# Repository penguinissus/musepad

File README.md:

# Musepad
This is a macropad that is built for helping with complicated functions when writing music in MuseScore. This macropad also features a compact and minimalistic design so it looks nice, and a plateless design which uses less material and provides more flex to each individual key.  

# User Instructions
Assembly:  
1. print out and buy all the parts found in `MusePad BOM.csv`   
2. solder everything together  
3. put in the keycaps accordingly (please refer to `3d models prints/Full Assembly.step` or reference pictures below for ideal layout)  
4. connect the oled to the pins on the PCB using jumper wires
5. sandwich pcb between the top and the bottom case  

Firmware:  
1. go to [circuitpython.org/downloads](circuitpython.org/downloads)    
2. download circuitpython for raspberry pi pico  
3. plug in keyboard to laptop and make sure to use a data transmitting cable  
4. open up the pico folder in your computer's directory  
5. replace the content of `code.py` in the pico folder with the one in this repo (`root://code/code.py`) 

# Why and how did I make it
I love composing music, and MuseScore is one great free composing software. However, whenever I want to compose efficiently, musescore hinders me significantly. Each detail I add to the music either requires too much shortcut memorization or it would take ages to find so I built MusePad to solve this problem. 

I first came up with some drawings of the design to make sure I knew how the layout kind of looked like. Then I made the schematic and PCB design on keycad, mostly following a tutorial (refer to the first resource link). I made the CAD on onshape mostly using skills I already had based on my past experiences, and for details that I don't really know, I referenced the hackpad guide (link no.2 in resource section). I also learned how to cad a keycap following a youtube tutorial (link no.3) which was really interesting. 

# Diagrams
Schematic Diagram:  
  
PCB Editor View:  
  
PCB Model:  
  
Assembled Model:  

# Resources
1. the   
2.   
3.

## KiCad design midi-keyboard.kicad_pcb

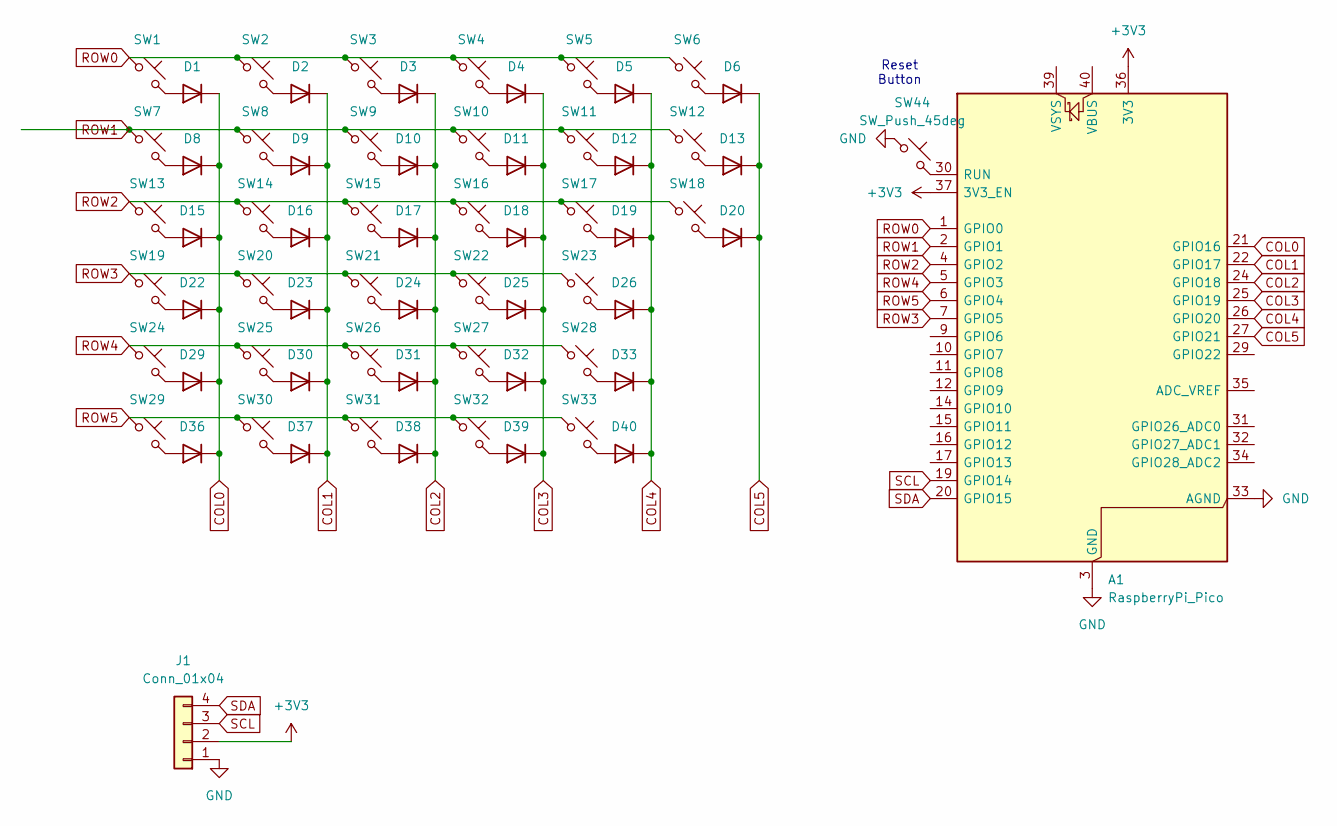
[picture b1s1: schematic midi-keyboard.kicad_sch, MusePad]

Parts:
A1: RaspberryPi_Pico; RaspberryPi_Pico_Common_THT
D1, D2, D3, D4, D5, D6, D8, D9, D10, D11, D12, D13, D15, D16, D17, D18, D19, D20, D22, D23, D24, D25, D26, D29, D30, D31, D32, D33, D36, D37, D38, D39, D40: 1N4148; D_DO-35_SOD27_P7.62mm_Horizontal
J1: Conn_01x04; PinSocket_1x04_P2.54mm_Vertical
SW1, SW2, SW3, SW4, SW5, SW6, SW7, SW8, SW9, SW10, SW11, SW12, SW13, SW14, SW15, SW16, SW17, SW18, SW19, SW20, SW21, SW22, SW23, SW24, SW25, SW26, SW27, SW28, SW29, SW30, SW31, SW32, SW33: SW_Push_45deg; SW_Cherry_MX_1.00u_PCB
SW44: SW_Push_45deg; SW_PUSH_6mm

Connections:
+3V3: A1.36 (3V3), A1.37 (3V3_EN), J1.2
COL0: A1.21 (GPIO16), D1.1 (K), D8.1 (K), D15.1 (K), D22.1 (K), D29.1 (K), D36.1 (K)
COL1: A1.22 (GPIO17), D2.1 (K), D9.1 (K), D16.1 (K), D23.1 (K), D30.1 (K), D37.1 (K)
COL2: A1.24 (GPIO18), D3.1 (K), D10.1 (K), D17.1 (K), D24.1 (K), D31.1 (K), D38.1 (K)
COL3: A1.25 (GPIO19), D4.1 (K), D11.1 (K), D18.1 (K), D25.1 (K), D32.1 (K), D39.1 (K)
COL4: A1.26 (GPIO20), D5.1 (K), D12.1 (K), D19.1 (K), D26.1 (K), D33.1 (K), D40.1 (K)
COL5: A1.27 (GPIO21), D6.1 (K), D13.1 (K), D20.1 (K)
GND: A1.3 (GND), A1.8 (GND), A1.13 (GND), A1.18 (GND), A1.23 (GND), A1.28 (GND), A1.33 (AGND), A1.38 (GND), J1.1, SW44.1
unnamed: A1.30 (RUN), SW44.2
unnamed: D1.2 (A), SW1.2
unnamed: D2.2 (A), SW2.2
unnamed: D3.2 (A), SW3.2
unnamed: D4.2 (A), SW4.2
unnamed: D5.2 (A), SW5.2
unnamed: D6.2 (A), SW6.2
unnamed: D8.2 (A), SW7.2
unnamed: D9.2 (A), SW8.2
unnamed: D10.2 (A), SW9.2
unnamed: D11.2 (A), SW10.2
unnamed: D12.2 (A), SW11.2
unnamed: D13.2 (A), SW12.2
unnamed: D15.2 (A), SW13.2
unnamed: D16.2 (A), SW14.2
unnamed: D17.2 (A), SW15.2
unnamed: D18.2 (A), SW16.2
unnamed: D19.2 (A), SW17.2
unnamed: D20.2 (A), SW18.2
unnamed: D22.2 (A), SW19.2
unnamed: D23.2 (A), SW20.2
unnamed: D24.2 (A), SW21.2
unnamed: D25.2 (A), SW22.2
unnamed: D26.2 (A), SW23.2
unnamed: D29.2 (A), SW24.2
unnamed: D30.2 (A), SW25.2
unnamed: D31.2 (A), SW26.2
unnamed: D32.2 (A), SW27.2
unnamed: D33.2 (A), SW28.2
unnamed: D36.2 (A), SW29.2
unnamed: D37.2 (A), SW30.2
unnamed: D38.2 (A), SW31.2
unnamed: D39.2 (A), SW32.2
unnamed: D40.2 (A), SW33.2
ROW0: A1.1 (GPIO0), SW1.1, SW2.1, SW3.1, SW4.1, SW5.1, SW6.1
ROW1: A1.2 (GPIO1), SW7.1, SW8.1, SW9.1, SW10.1, SW11.1, SW12.1
ROW2: A1.4 (GPIO2), SW13.1, SW14.1, SW15.1, SW16.1, SW17.1, SW18.1
ROW3: A1.7 (GPIO5), SW19.1, SW20.1, SW21.1, SW22.1, SW23.1
ROW4: A1.5 (GPIO3), SW24.1, SW25.1, SW26.1, SW27.1, SW28.1
ROW5: A1.6 (GPIO4), SW29.1, SW30.1, SW31.1, SW32.1, SW33.1
SCL: A1.19 (GPIO14), J1.3
SDA: A1.20 (GPIO15), J1.4

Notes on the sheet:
Reset Button

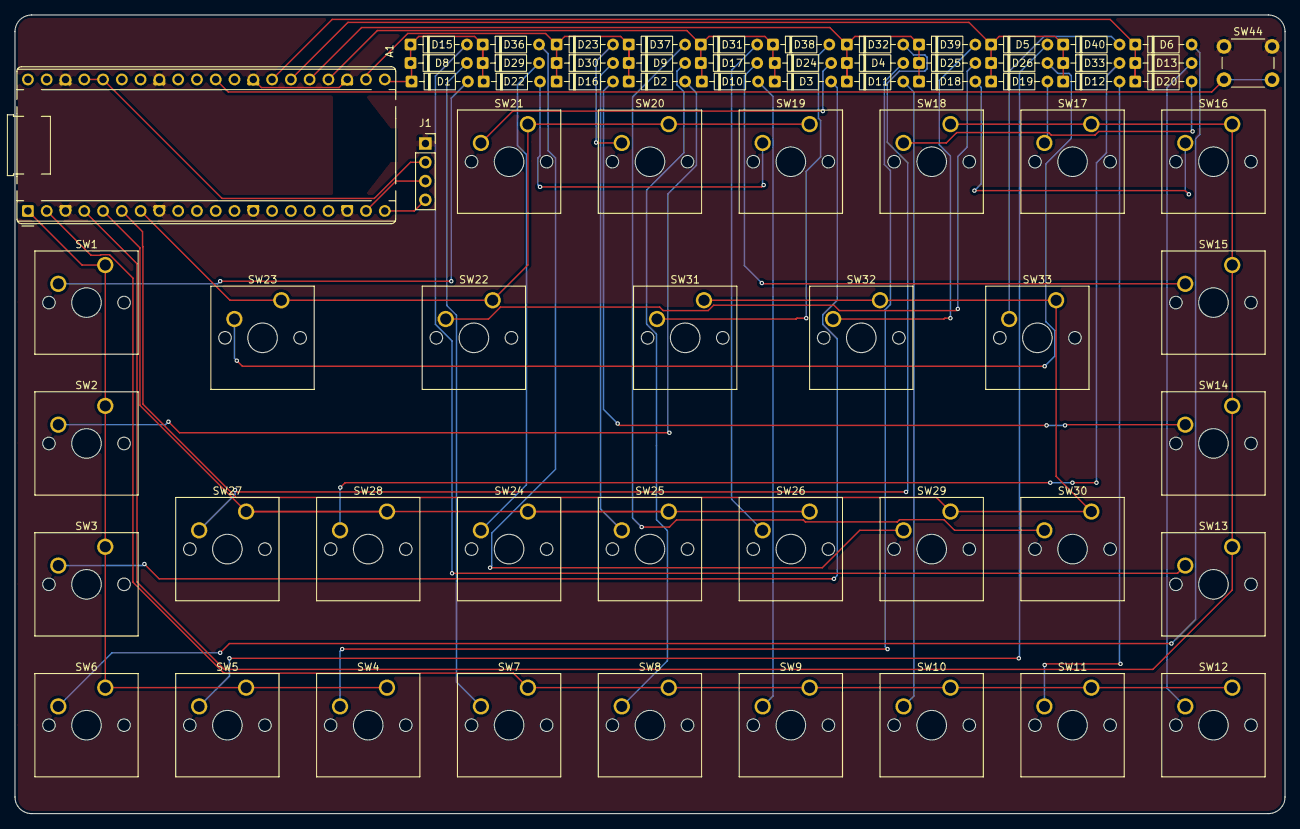
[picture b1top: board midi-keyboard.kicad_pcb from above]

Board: 2 copper layers, 171.8 x 108.0 mm, 69 parts (0 on the bottom side), 50 nets.

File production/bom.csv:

Designator,Footprint,Quantity,Value,LCSC Part #
A1,RaspberryPi_Pico_Common_THT,1,RaspberryPi_Pico,
"D1, D10, D11, D12, D13, D15, D16, D17, D18, D19, D2, D20, D22, D23, D24, D25, D26, D29, D3, D30, D31, D32, D33, D36, D37, D38, D39, D4, D40, D5, D6, D8, D9",D_DO-35_SOD27_P7.62mm_Horizontal,33,1N4148,
J1,PinSocket_1x04_P2.54mm_Vertical,1,Conn_01x04,
"SW1, SW10, SW11, SW12, SW13, SW14, SW15, SW16, SW17, SW18, SW19, SW2, SW20, SW21, SW22, SW23, SW24, SW25, SW26, SW27, SW28, SW29, SW3, SW30, SW31, SW32, SW33, SW4, SW5, SW6, SW7, SW8, SW9",SW_Cherry_MX_1.00u_PCB,33,SW_Push_45deg,
SW44,SW_PUSH_6mm,1,SW_Push_45deg,

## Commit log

2026-06-19 updated schematic
2026-06-19 finished pcb tracing
2026-06-20 added 3d model files
2026-06-20 add 3d model
2026-06-20 production files
2026-06-20 readme
2026-06-20 swap keys
2026-06-20 rough draft of code
2026-06-20 code
2026-06-20 adafruit library
2026-06-20 zine
2026-06-20 reorganize repo
2026-06-20 add onshape link
2026-06-27 update bom
2026-06-28 update cad
